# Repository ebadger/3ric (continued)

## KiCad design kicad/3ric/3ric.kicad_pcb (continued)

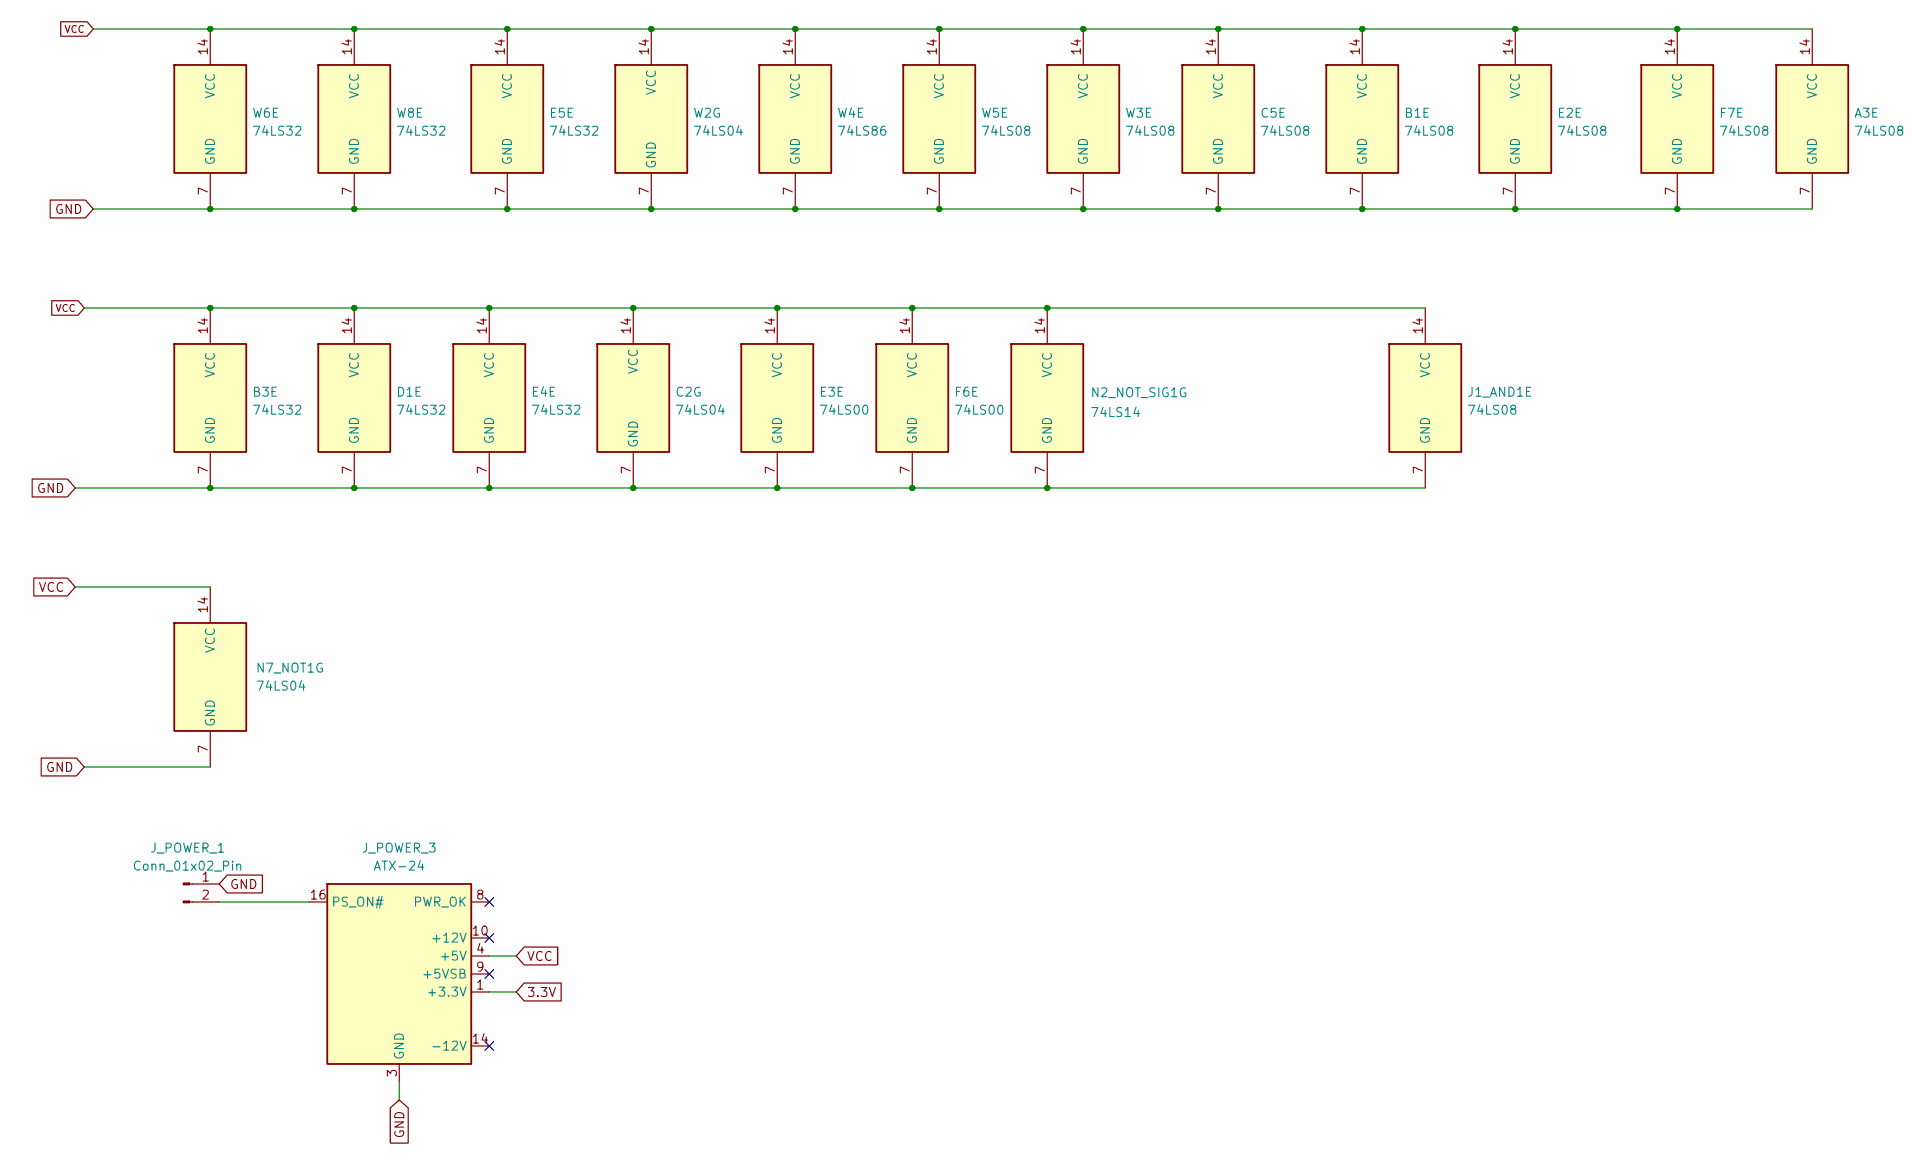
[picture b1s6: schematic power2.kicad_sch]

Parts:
A3: 74LS08; DIP-14_W7.62mm_Socket
B1: 74LS08; DIP-14_W7.62mm_Socket
B3: 74LS32; DIP-14_W7.62mm_Socket
C2: 74LS04; DIP-14_W7.62mm_Socket
C5: 74LS08; DIP-14_W7.62mm_Socket
D1: 74LS32; DIP-14_W7.62mm_Socket
E2: 74LS08; DIP-14_W7.62mm_Socket
E3: 74LS00; DIP-14_W7.62mm_Socket
E4, E5: 74LS32; DIP-14_W7.62mm_Socket
F6: 74LS00; DIP-14_W7.62mm_Socket
F7: 74LS08; DIP-14_W7.62mm_Socket
J1_AND1: 74LS08; DIP-14_W7.62mm_Socket
J_POWER_1: Conn_01x02_Pin; PinHeader_2x01_P2.54mm_Vertical
J_POWER_3: ATX-24; 1-1775099-3
N2_NOT_SIG1: 74LS14; DIP-14_W7.62mm_Socket
N7_NOT1: 74LS04; DIP-14_W7.62mm_Socket
W2: 74LS04; DIP-14_W7.62mm_Socket
W3, W5: 74LS08; DIP-14_W7.62mm_Socket
W4: 74LS86; DIP-14_W7.62mm_Socket
W6, W8: 74LS32; DIP-14_W7.62mm_Socket

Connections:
3.3V: J_POWER_3.1 (+3.3V), J_POWER_3.2 (+3.3V), J_POWER_3.12 (+3.3V), J_POWER_3.13 (+3.3V); also elsewhere on the board
GND: A3.7 (GND), B1.7 (GND), B3.7 (GND), C2.7 (GND), C5.7 (GND), D1.7 (GND), E2.7 (GND), E3.7 (GND), E4.7 (GND), E5.7 (GND), F6.7 (GND), F7.7 (GND), J1_AND1.7 (GND), J_POWER_1.1, J_POWER_3.3 (GND), J_POWER_3.5 (GND), J_POWER_3.7 (GND), J_POWER_3.15 (GND), J_POWER_3.17 (GND), J_POWER_3.18 (GND), J_POWER_3.19 (GND), J_POWER_3.24 (GND), N2_NOT_SIG1.7 (GND), N7_NOT1.7 (GND), W2.7 (GND), W3.7 (GND), W4.7 (GND), W5.7 (GND), W6.7 (GND), W8.7 (GND); also elsewhere on the board
unnamed: J_POWER_1.2, J_POWER_3.16 (PS_ON#)
VCC: A3.14 (VCC), B1.14 (VCC), B3.14 (VCC), C2.14 (VCC), C5.14 (VCC), D1.14 (VCC), E2.14 (VCC), E3.14 (VCC), E4.14 (VCC), E5.14 (VCC), F6.14 (VCC), F7.14 (VCC), J1_AND1.14 (VCC), J_POWER_3.4 (+5V), J_POWER_3.6 (+5V), J_POWER_3.21 (+5V), J_POWER_3.22 (+5V), J_POWER_3.23 (+5V), N2_NOT_SIG1.14 (VCC), N7_NOT1.14 (VCC), W2.14 (VCC), W3.14 (VCC), W4.14 (VCC), W5.14 (VCC), W6.14 (VCC), W8.14 (VCC); also elsewhere on the board

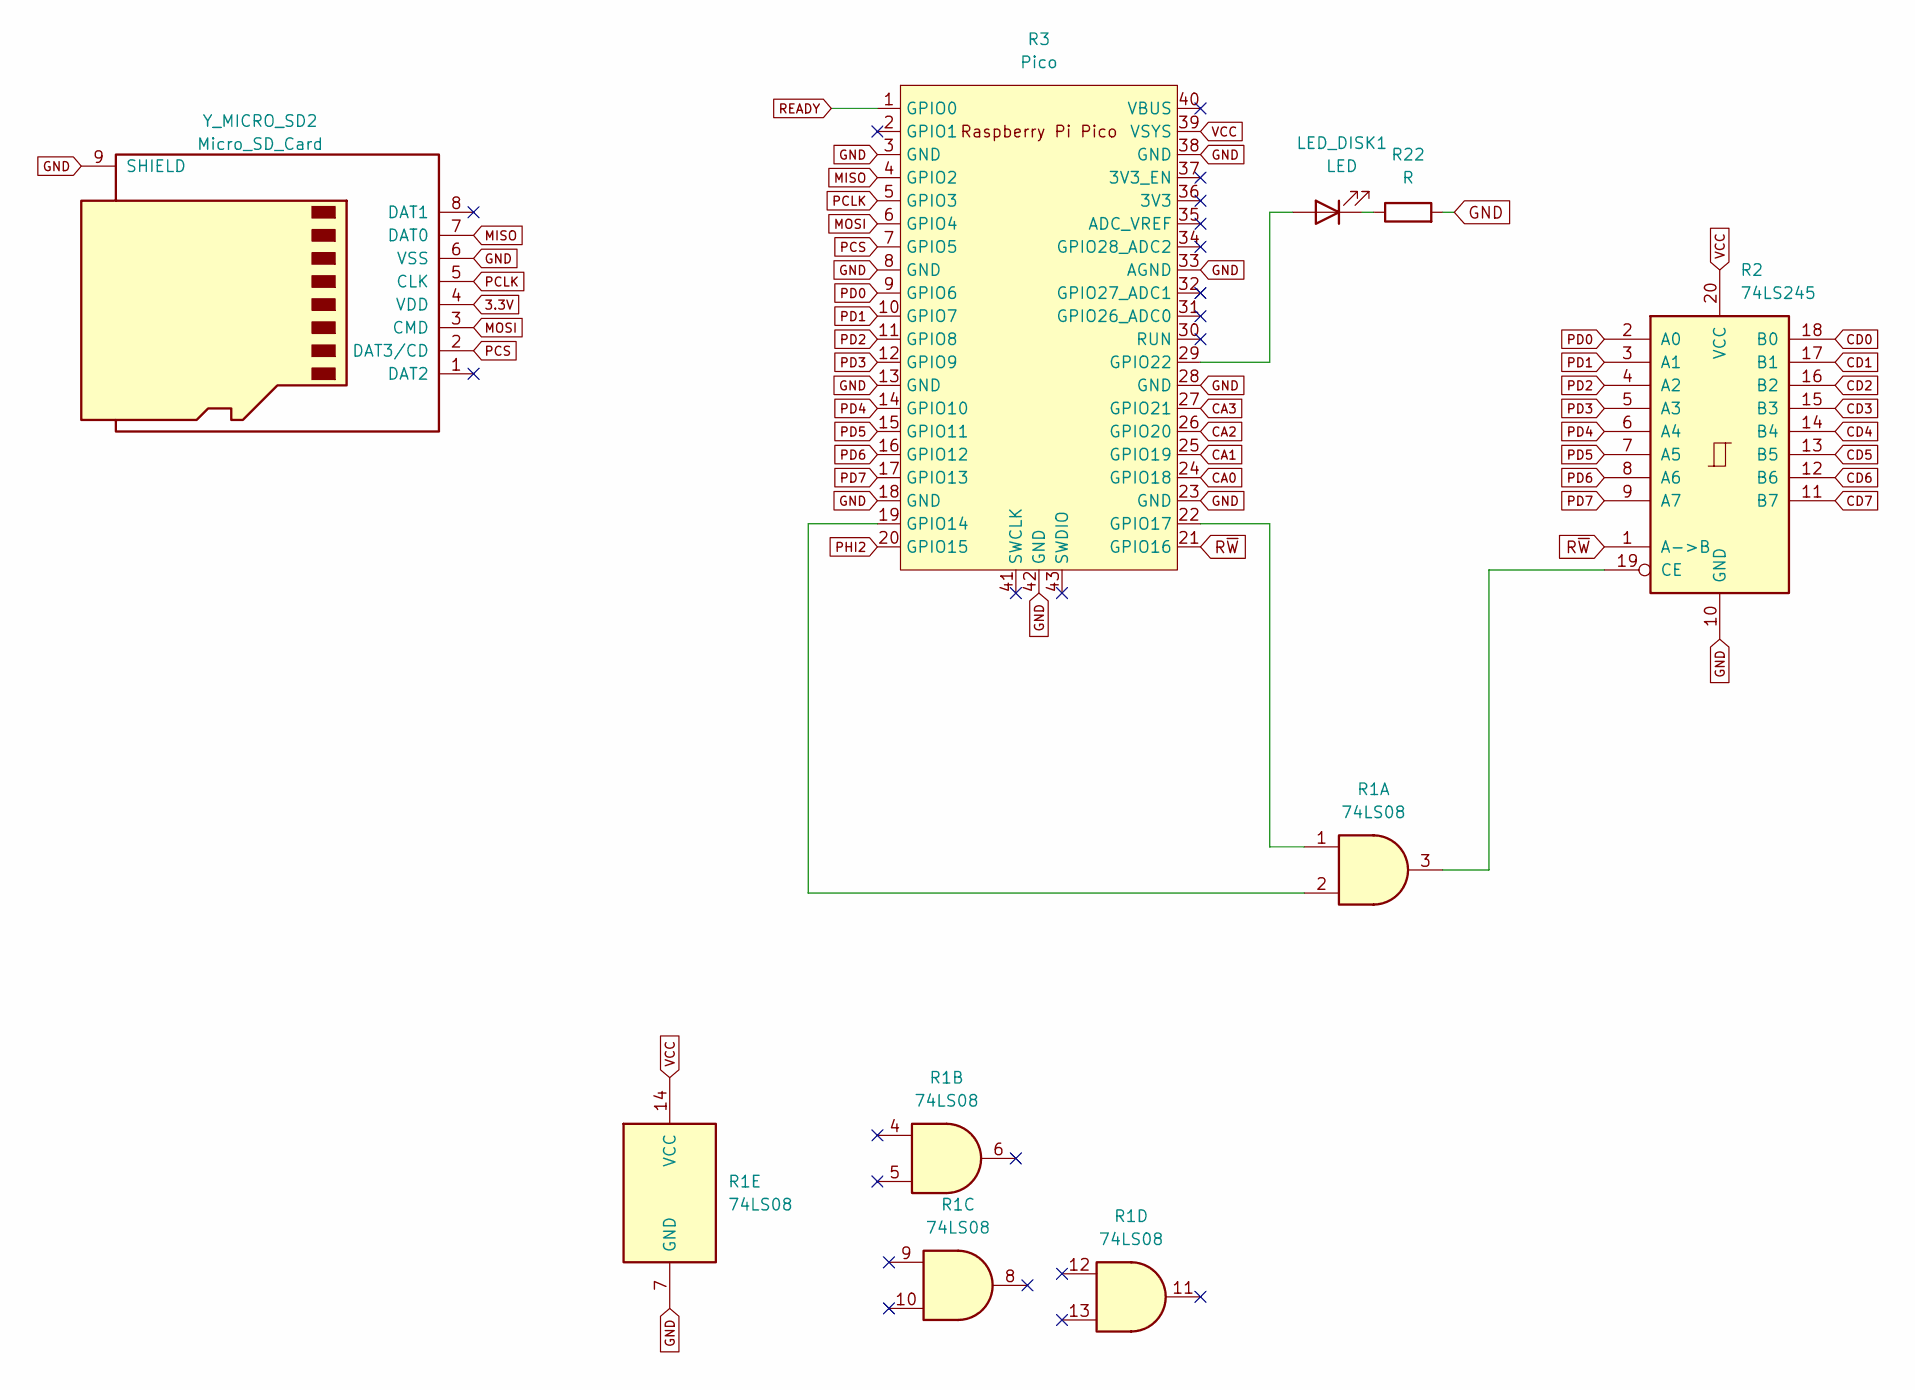
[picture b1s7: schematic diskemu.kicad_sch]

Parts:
LED_DISK1: LED; LED_D5.0mm
R1: 74LS08; DIP-14_W7.62mm_Socket
R2: 74LS245; DIP-20_W7.62mm_Socket
R3: Pico; RPi_Pico_SMD_TH
R22: R; R_0603_1608Metric_Pad0.98x0.95mm_HandSolder
Y_MICRO_SD2: Micro_SD_Card; microSD_Amazon2

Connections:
3.3V: Y_MICRO_SD2.4 (VDD); also elsewhere on the board
CA0: R3.24 (GPIO18); also elsewhere on the board
CA1: R3.25 (GPIO19); also elsewhere on the board
CA2: R3.26 (GPIO20); also elsewhere on the board
CA3: R3.27 (GPIO21); also elsewhere on the board
CD0: R2.18 (B0); also elsewhere on the board
CD1: R2.17 (B1); also elsewhere on the board
CD2: R2.16 (B2); also elsewhere on the board
CD3: R2.15 (B3); also elsewhere on the board
CD4: R2.14 (B4); also elsewhere on the board
CD5: R2.13 (B5); also elsewhere on the board
CD6: R2.12 (B6); also elsewhere on the board
CD7: R2.11 (B7); also elsewhere on the board
GND: R1.7 (GND), R2.10 (GND), R3.3 (GND), R3.8 (GND), R3.13 (GND), R3.18 (GND), R3.23 (GND), R3.28 (GND), R3.33 (AGND), R3.38 (GND), R3.42 (GND), R22.2, Y_MICRO_SD2.6 (VSS), Y_MICRO_SD2.9 (SHIELD); also elsewhere on the board
MISO: R3.4 (GPIO2), Y_MICRO_SD2.7 (DAT0)
MOSI: R3.6 (GPIO4), Y_MICRO_SD2.3 (CMD)
unnamed: LED_DISK1.2 (A), R3.29 (GPIO22)
unnamed: LED_DISK1.1 (K), R22.1
unnamed: R1.3, R2.19 (CE)
unnamed: R1.2, R3.19 (GPIO14)
unnamed: R1.1, R3.22 (GPIO17)
PCLK: R3.5 (GPIO3), Y_MICRO_SD2.5 (CLK)
PCS: R3.7 (GPIO5), Y_MICRO_SD2.2 (DAT3/CD)
PD0: R2.2 (A0), R3.9 (GPIO6)
PD1: R2.3 (A1), R3.10 (GPIO7)
PD2: R2.4 (A2), R3.11 (GPIO8)
PD3: R2.5 (A3), R3.12 (GPIO9)
PD4: R2.6 (A4), R3.14 (GPIO10)
PD5: R2.7 (A5), R3.15 (GPIO11)
PD6: R2.8 (A6), R3.16 (GPIO12)
PD7: R2.9 (A7), R3.17 (GPIO13)
PHI2: R3.20 (GPIO15); also elsewhere on the board
READY: R3.1 (GPIO0); also elsewhere on the board
R~W: R2.1 (A->B), R3.21 (GPIO16); also elsewhere on the board
VCC: R1.14 (VCC), R2.20 (VCC), R3.39 (VSYS); also elsewhere on the board

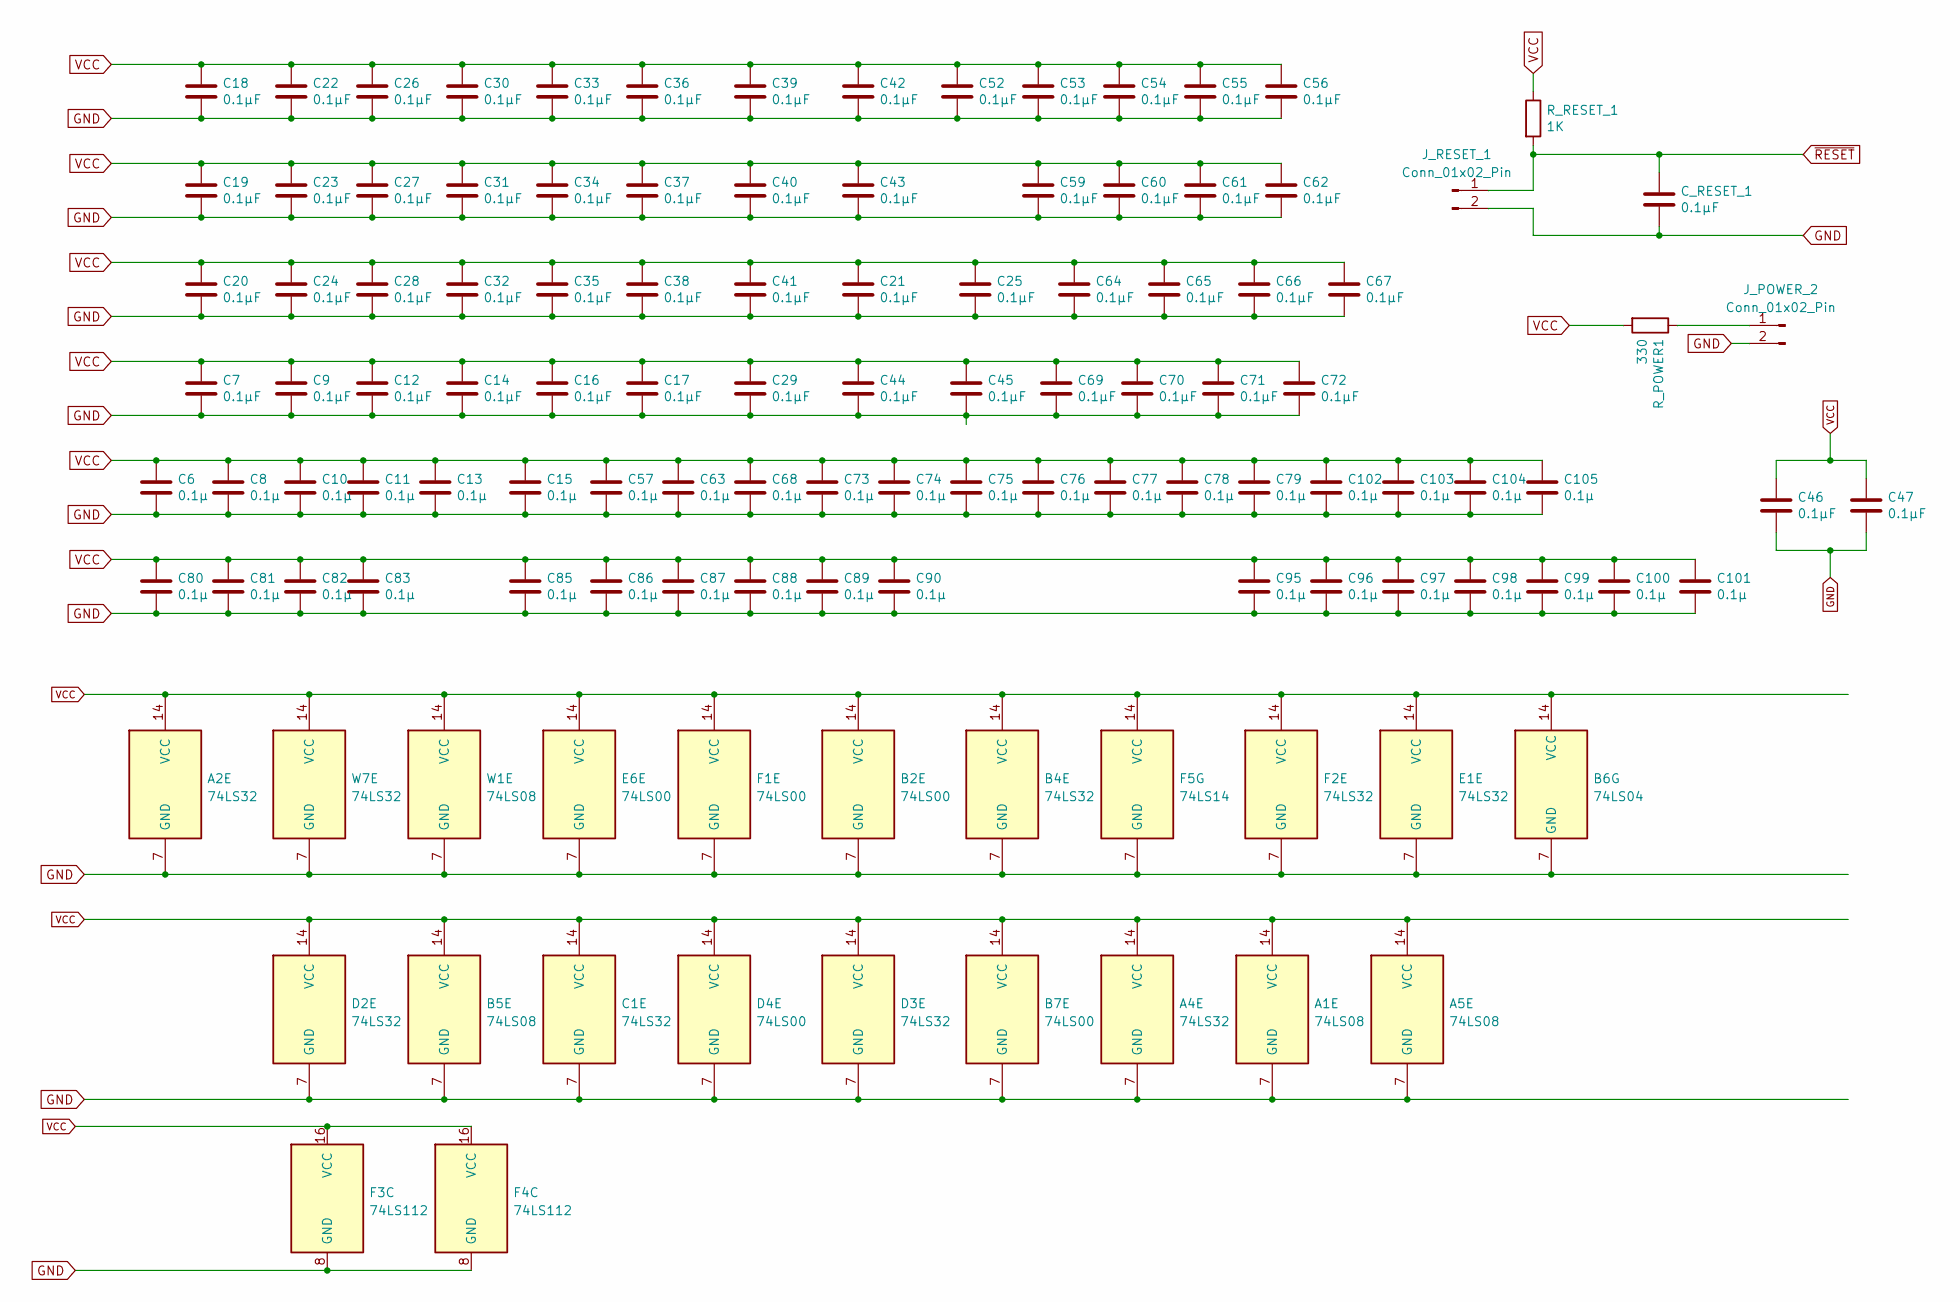
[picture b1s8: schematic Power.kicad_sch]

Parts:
A1, A5: 74LS08; DIP-14_W7.62mm_Socket
A2, A4: 74LS32; DIP-14_W7.62mm_Socket
B2, B7: 74LS00; DIP-14_W7.62mm_Socket
B4: 74LS32; DIP-14_W7.62mm_Socket
B5: 74LS08; DIP-14_W7.62mm_Socket
B6: 74LS04; DIP-14_W7.62mm_Socket
C1: 74LS32; DIP-14_W7.62mm_Socket
C6, C8, C10, C11, C13, C15, C57, C63, C68, C73, C74, C75, C76, C77, C78, C79, C80, C81, C82, C83, C85, C86, C87, C88, C89, C90, C95, C96, C97, C98, C99, C100, C101, C102, C103, C104, C105: 0.1µ; C_1206_3216Metric_Pad1.33x1.80mm_HandSolder
C7, C9, C12, C14, C16, C17, C18, C19, C20, C21, C22, C23, C24, C25, C26, C27, C28, C29, C30, C31, C32, C33, C34, C35, C36, C37, C38, C39, C40, C41, C42, C43, C44, C45, C46, C47, C52, C53, C54, C55, C56, C59, C60, C61, C62, C64, C65, C66, C67, C69, C70, C71, C72: 0.1µF; C_1206_3216Metric_Pad1.33x1.80mm_HandSolder
C_RESET_1: 0.1µF; C_1206_3216Metric_Pad1.33x1.80mm_HandSolder
D2, D3: 74LS32; DIP-14_W7.62mm_Socket
D4: 74LS00; DIP-14_W7.62mm_Socket
E1: 74LS32; DIP-14_W7.62mm_Socket
E6: 74LS00; DIP-14_W7.62mm_Socket
F1: 74LS00; DIP-14_W7.62mm_Socket
F2: 74LS32; DIP-14_W7.62mm_Socket
F3, F4: 74LS112; DIP-16_W7.62mm_Socket
F5: 74LS14; DIP-14_W7.62mm_Socket
J_POWER_2: Conn_01x02_Pin; PinHeader_2x01_P2.54mm_Vertical
J_RESET_1: Conn_01x02_Pin; PinHeader_2x01_P2.54mm_Vertical
R_POWER1: 330; R_0603_1608Metric_Pad0.98x0.95mm_HandSolder
R_RESET_1: 1K; R_0805_2012Metric_Pad1.20x1.40mm_HandSolder
W1: 74LS08; DIP-14_W7.62mm_Socket
W7: 74LS32; DIP-14_W7.62mm_Socket

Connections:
GND: A1.7 (GND), A2.7 (GND), A4.7 (GND), A5.7 (GND), B2.7 (GND), B4.7 (GND), B5.7 (GND), B6.7 (GND), B7.7 (GND), C1.7 (GND), C6.2, C7.2, C8.2, C9.2, C10.2, C11.2, C12.2, C13.2, C14.2, C15.2, C16.2, C17.2, C18.2, C19.2, C20.2, C21.2, C22.2, C23.2, C24.2, C25.2, C26.2, C27.2, C28.2, C29.2, C30.2, C31.2, C32.2, C33.2, C34.2, C35.2, C36.2, C37.2, C38.2, C39.2, C40.2, C41.2, C42.2, C43.2, C44.2, C45.2, C46.2, C47.2, C52.2, C53.2, C54.2, C55.2, C56.2, C57.2, C59.2, C60.2, C61.2, C62.2, C63.2, C64.2, C65.2, C66.2, C67.2, C68.2, C69.2, C70.2, C71.2, C72.2, C73.2, C74.2, C75.2, C76.2, C77.2, C78.2, C79.2, C80.2, C81.2, C82.2, C83.2, C85.2, C86.2, C87.2, C88.2, C89.2, C90.2, C95.2, C96.2, C97.2, C98.2, C99.2, C100.2, C101.2, C102.2, C103.2, C104.2, C105.2, C_RESET_1.2, D2.7 (GND), D3.7 (GND), D4.7 (GND), E1.7 (GND), E6.7 (GND), F1.7 (GND), F2.7 (GND), F3.8 (GND), F4.8 (GND), F5.7 (GND), J_POWER_2.2, J_RESET_1.2, W1.7 (GND), W7.7 (GND); also elsewhere on the board
unnamed: J_POWER_2.1, R_POWER1.1
VCC: A1.14 (VCC), A2.14 (VCC), A4.14 (VCC), A5.14 (VCC), B2.14 (VCC), B4.14 (VCC), B5.14 (VCC), B6.14 (VCC), B7.14 (VCC), C1.14 (VCC), C6.1, C7.1, C8.1, C9.1, C10.1, C11.1, C12.1, C13.1, C14.1, C15.1, C16.1, C17.1, C18.1, C19.1, C20.1, C21.1, C22.1, C23.1, C24.1, C25.1, C26.1, C27.1, C28.1, C29.1, C30.1, C31.1, C32.1, C33.1, C34.1, C35.1, C36.1, C37.1, C38.1, C39.1, C40.1, C41.1, C42.1, C43.1, C44.1, C45.1, C46.1, C47.1, C52.1, C53.1, C54.1, C55.1, C56.1, C57.1, C59.1, C60.1, C61.1, C62.1, C63.1, C64.1, C65.1, C66.1, C67.1, C68.1, C69.1, C70.1, C71.1, C72.1, C73.1, C74.1, C75.1, C76.1, C77.1, C78.1, C79.1, C80.1, C81.1, C82.1, C83.1, C85.1, C86.1, C87.1, C88.1, C89.1, C90.1, C95.1, C96.1, C97.1, C98.1, C99.1, C100.1, C101.1, C102.1, C103.1, C104.1, C105.1, D2.14 (VCC), D3.14 (VCC), D4.14 (VCC), E1.14 (VCC), E6.14 (VCC), F1.14 (VCC), F2.14 (VCC), F3.16 (VCC), F4.16 (VCC), F5.14 (VCC), R_POWER1.2, R_RESET_1.1, W1.14 (VCC), W7.14 (VCC); also elsewhere on the board
~RESET: C_RESET_1.1, J_RESET_1.1, R_RESET_1.2; also elsewhere on the board

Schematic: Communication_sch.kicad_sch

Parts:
H1_LEVEL_SHIFT1: ETSSOP-20-1EP_4.4x6.5mm_P0.65mm_EP3x4.2mm
H2_ACIA_CLK1: 1.8432MHz; Oscillator_DIP-14
I1_VIA1: 65C22S; DIP-40_W15.24mm_Socket
J4_ACIA1: 6502-library_65C51N; DIP-28_W15.24mm_Socket
J5, J6: Conn_02x08_Odd_Even; PinHeader_2x08_P2.54mm_Vertical
RKB1, RKB2: R; R_0805_2012Metric_Pad1.20x1.40mm_HandSolder
RM1, RM2: R; R_0805_2012Metric_Pad1.20x1.40mm_HandSolder
Y_MICRO_SD1: Micro_SD_Card; microSD_Amazon2
Y_PS2_KB1: PS/2 keyboard; MINI-DIN-6-FULL-SHIELD
Y_PS2_MOUSE1: PS/2 Mouse; MINI-DIN-6-FULL-SHIELD
Y_SERIAL_PINS1: PinHeader_2x03_P2.54mm_Vertical
Y_SNES_1, Y_SNES_2: SNES_Controller_Socket

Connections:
3.3V: H1_LEVEL_SHIFT1.2 (VCCA), Y_MICRO_SD1.4 (VDD); also elsewhere on the board
C010: I1_VIA1.18 (CB1); also elsewhere on the board
C070: I1_VIA1.19 (CB2); also elsewhere on the board
CA0: I1_VIA1.38 (RS0), J4_ACIA1.13 (RS0), J5.1; also elsewhere on the board
CA1: I1_VIA1.37 (RS1), J4_ACIA1.14 (RS1), J5.3; also elsewhere on the board
CA2: I1_VIA1.36 (RS2), J5.5; also elsewhere on the board
CA3: I1_VIA1.35 (RS3), J5.7; also elsewhere on the board
CA4: J5.9; also elsewhere on the board
CA5: J5.11; also elsewhere on the board
CA6: J5.13; also elsewhere on the board
CA7: J5.15; also elsewhere on the board
CA8: J5.10; also elsewhere on the board
CA9: J5.12; also elsewhere on the board
CA10: J5.14; also elsewhere on the board
CA11: J5.16; also elsewhere on the board
CA12: J5.8; also elsewhere on the board
CA13: J5.6; also elsewhere on the board
CA14: J5.4; also elsewhere on the board
CA15: J5.2; also elsewhere on the board
CD0: I1_VIA1.33 (D0), J4_ACIA1.18 (D0), J6.6; also elsewhere on the board
CD1: I1_VIA1.32 (D1), J4_ACIA1.19 (D1), J6.4; also elsewhere on the board
CD2: I1_VIA1.31 (D2), J4_ACIA1.20 (D2), J6.2; also elsewhere on the board
CD3: I1_VIA1.30 (D3), J4_ACIA1.21 (D3), J6.8; also elsewhere on the board
CD4: I1_VIA1.29 (D4), J4_ACIA1.22 (D4), J6.10; also elsewhere on the board
CD5: I1_VIA1.28 (D5), J4_ACIA1.23 (D5), J6.12; also elsewhere on the board
CD6: I1_VIA1.27 (D6), J4_ACIA1.24 (D6), J6.14; also elsewhere on the board
CD7: I1_VIA1.26 (D7), J4_ACIA1.25 (D7), J6.16; also elsewhere on the board
CLK_KB: I1_VIA1.8 (PA6), I1_VIA1.39 (CA2), RKB1.2, Y_PS2_KB1.5
CLK_MOUSE: I1_VIA1.11 (PB1), I1_VIA1.40 (CA1), RM1.2, Y_PS2_MOUSE1.5
DATA_KB: I1_VIA1.9 (PA7), RKB2.1, Y_PS2_KB1.1
DATA_MOUSE: I1_VIA1.10 (PB0), RM2.1, Y_PS2_MOUSE1.1
GC_CLOCK: I1_VIA1.17 (PB7), Y_SNES_1.2 (Clock), Y_SNES_2.2 (Clock)
GC_DATA1: I1_VIA1.15 (PB5), Y_SNES_1.4 (Data)
GC_DATA2: I1_VIA1.14 (PB4), Y_SNES_2.4 (Data)
GC_LATCH: I1_VIA1.16 (PB6), Y_SNES_1.3 (Latch), Y_SNES_2.3 (Latch)
GND: H1_LEVEL_SHIFT1.11 (GND), H2_ACIA_CLK1.7 (GND), I1_VIA1.1 (VSS), J4_ACIA1.1 (VSS), J6.5, Y_MICRO_SD1.6 (VSS), Y_MICRO_SD1.9 (SHIELD), Y_PS2_KB1.3, Y_PS2_MOUSE1.3, Y_SERIAL_PINS1.2, Y_SNES_1.7 (GND), Y_SNES_2.7 (GND); also elsewhere on the board
unnamed: H1_LEVEL_SHIFT1.1 (A1), Y_MICRO_SD1.7 (DAT0)
unnamed: H1_LEVEL_SHIFT1.3 (A2), Y_MICRO_SD1.3 (CMD)
unnamed: H1_LEVEL_SHIFT1.4 (A3), Y_MICRO_SD1.5 (CLK)
unnamed: H1_LEVEL_SHIFT1.5 (A4), Y_MICRO_SD1.2 (DAT3/CD)
unnamed: H1_LEVEL_SHIFT1.20 (B1), I1_VIA1.3 (PA1)
unnamed: H1_LEVEL_SHIFT1.18 (B2), I1_VIA1.4 (PA2)
unnamed: H1_LEVEL_SHIFT1.17 (B3), I1_VIA1.5 (PA3)
unnamed: H1_LEVEL_SHIFT1.16 (B4), I1_VIA1.6 (PA4)
unnamed: H2_ACIA_CLK1.8 (OUT), J4_ACIA1.6 (XTLI)
PHI2: I1_VIA1.25 (PHI2), J4_ACIA1.27 (PHI2), J6.11; also elsewhere on the board
RXD: J4_ACIA1.12 (RxD), Y_SERIAL_PINS1.5
R~W: I1_VIA1.22 (R~W), J4_ACIA1.28 (R~W), J6.13; also elsewhere on the board
TXD: J4_ACIA1.10 (TxD), Y_SERIAL_PINS1.6
V1_A0: I1_VIA1.2 (PA0)
V1_B2: I1_VIA1.12 (PB2)
V1_B3: I1_VIA1.13 (PB3)
VCC: H1_LEVEL_SHIFT1.10 (OE), H1_LEVEL_SHIFT1.19 (VCCB), H2_ACIA_CLK1.14 (Vcc), I1_VIA1.20 (VDD), I1_VIA1.24 (CS1), J4_ACIA1.2 (CS0), J4_ACIA1.15 (VDD), J6.15, RKB1.1, RKB2.2, RM1.1, RM2.2, Y_PS2_KB1.4, Y_PS2_MOUSE1.4, Y_SERIAL_PINS1.1, Y_SNES_1.1 (VCC), Y_SNES_2.1 (VCC); also elsewhere on the board
~CS_ACIA: J4_ACIA1.3 (~CS1); also elsewhere on the board
~CS_IO5: J6.3; also elsewhere on the board
~CS_IO7: J6.1; also elsewhere on the board
~CS_VIA1: I1_VIA1.23 (~CS2); also elsewhere on the board
~CTS: J4_ACIA1.9 (~CTS), Y_SERIAL_PINS1.4
~IRQEXT: J6.9; also elsewhere on the board
~IRQ_ACIA: J4_ACIA1.26 (~IRQ); also elsewhere on the board
~IRQ_VIA1: I1_VIA1.21 (~IRQ); also elsewhere on the board
~NMIEXT: J6.7; also elsewhere on the board
~RESET: I1_VIA1.34 (~RES), J4_ACIA1.4 (~RES); also elsewhere on the board
~RTS: J4_ACIA1.8 (~RTS), Y_SERIAL_PINS1.3

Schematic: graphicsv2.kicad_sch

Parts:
D20, D21, D22, D23, D24: D; D_SMA-SMB_Universal_Handsoldering
R_BLUE_220: 220; R_0603_1608Metric_Pad0.98x0.95mm_HandSolder
R_BLUE_500: 500; R_0805_2012Metric_Pad1.20x1.40mm_HandSolder
R_DOWN1: 100; R_0402_1005Metric_Pad0.72x0.64mm_HandSolder
R_GREEN_220: 220; R_0603_1608Metric_Pad0.98x0.95mm_HandSolder
R_GREEN_500: 500; R_0805_2012Metric_Pad1.20x1.40mm_HandSolder
R_RED_220: 220; R_0603_1608Metric_Pad0.98x0.95mm_HandSolder
R_RED_500: 500; R_0805_2012Metric_Pad1.20x1.40mm_HandSolder
U1_VID_SHIFT1, U2_PIXEL_LATCH1, U3_LOWRES_OUT1: DIP-20_W7.62mm_Socket
U4_ODD_BIT1: DIP-16_W7.62mm_Socket
V1_PALETTE_LATCH1, V2_PHI16_LATCH1: DIP-20_W7.62mm_Socket
W1, W3, W5: 74LS08; DIP-14_W7.62mm_Socket
W2: 74LS04; DIP-14_W7.62mm_Socket
W4: 74LS86; DIP-14_W7.62mm_Socket
W6, W7, W8: 74LS32; DIP-14_W7.62mm_Socket
Y_VGA1: DB15_Female_HighDensity; DSUB-15-HD_Female_Horizontal_P2.29x1.98mm_EdgePinOffset8.35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

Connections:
!DISPLAY2: V2_PHI16_LATCH1.1 (OE), W7.13; also elsewhere on the board
!GFXSHIFT: U1_VID_SHIFT1.9 (Mr); also elsewhere on the board
B1: D22.1 (K), R_BLUE_220.1, U3_LOWRES_OUT1.14 (Q5); also elsewhere on the board
B2: D23.1 (K), R_BLUE_500.1, U3_LOWRES_OUT1.15 (Q4); also elsewhere on the board
CYAN: W5.11, W6.10, W6.12, W7.1
CurrPix: U2_PIXEL_LATCH1.4 (D2), U2_PIXEL_LATCH1.18 (Q1), W1.2
DISP3OUT: U2_PIXEL_LATCH1.15 (Q4), W1.1, W1.4
DISPLAY3: U2_PIXEL_LATCH1.6 (D4), U4_ODD_BIT1.1 (~MR); also elsewhere on the board
G1: D20.1 (K), R_GREEN_220.1, U3_LOWRES_OUT1.16 (Q3)
G2: D21.1 (K), R_GREEN_500.1, U3_LOWRES_OUT1.17 (Q2)
GFXLOAD: U1_VID_SHIFT1.19 (S1), U3_LOWRES_OUT1.11 (Cp); also elsewhere on the board
GND: R_DOWN1.2, U1_VID_SHIFT1.10 (GND), U1_VID_SHIFT1.11 (Ds0), U1_VID_SHIFT1.18 (Ds7), U2_PIXEL_LATCH1.1 (OE), U2_PIXEL_LATCH1.7 (D5), U2_PIXEL_LATCH1.8 (D6), U2_PIXEL_LATCH1.9 (D7), U2_PIXEL_LATCH1.10 (GND), U3_LOWRES_OUT1.10 (GND), U4_ODD_BIT1.3 (D0), U4_ODD_BIT1.4 (D1), U4_ODD_BIT1.5 (D2), U4_ODD_BIT1.6 (D3), U4_ODD_BIT1.8 (GND), V1_PALETTE_LATCH1.1 (OE), V1_PALETTE_LATCH1.10 (GND), V2_PHI16_LATCH1.10 (GND), Y_VGA1.5, Y_VGA1.6, Y_VGA1.7, Y_VGA1.8, Y_VGA1.10; also elsewhere on the board
GREEN: W5.6, W6.5, W8.10
HGR_B1: D22.2 (A), W8.11
HGR_B2: D23.2 (A), W8.3
HGR_G1: D20.2 (A), W8.6
HGR_G2: D21.2 (A), W8.8
HGR_R1: D24.2 (A), W7.8
HSYNC: Y_VGA1.13; also elsewhere on the board
LOWOUT: U3_LOWRES_OUT1.1 (OE), W7.11
LOWSHIFT: W7.12; also elsewhere on the board
unnamed: R_BLUE_220.2, R_BLUE_500.2, Y_VGA1.3
unnamed: R_GREEN_220.2, R_GREEN_500.2, Y_VGA1.2
unnamed: R_RED_220.2, R_RED_500.2, Y_VGA1.1
unnamed: U1_VID_SHIFT1.17 (Q7), U2_PIXEL_LATCH1.3 (D1)
unnamed: W1.3, W2.1, W3.1, W3.4
unnamed: W1.6, W2.3, W3.5, W3.9
unnamed: W1.8, W4.5, W4.9
unnamed: W1.10, W4.3
unnamed: W2.2, W3.10
unnamed: W2.4, W3.2
unnamed: W2.6, W5.5, W5.9
unnamed: W3.3, W4.1, W4.4
unnamed: W3.8, W4.2, W4.10
unnamed: W4.6, W5.1, W5.4
unnamed: W4.8, W5.10, W5.12
unnamed: W6.3, W6.9, W7.10
unnamed: W6.6, W7.2
unnamed: W6.8, W8.12
unnamed: W6.11, W8.1
unnamed: W7.3, W8.4
unnamed: W7.6, W7.9, W8.2, W8.5, W8.9, W8.13
ORANGE: W5.3, W6.1, W6.4
OddBit1: U2_PIXEL_LATCH1.5 (D3), U4_ODD_BIT1.14 (Q0)
OddBit2: U2_PIXEL_LATCH1.16 (Q3), W1.9
PAL_IN: U2_PIXEL_LATCH1.2 (D0), V1_PALETTE_LATCH1.12 (Q7)
PHI7: U1_VID_SHIFT1.12 (Cp), U2_PIXEL_LATCH1.11 (Cp), U4_ODD_BIT1.2 (CP); also elsewhere on the board
PHI16: V2_PHI16_LATCH1.11 (Cp); also elsewhere on the board
Palette: U2_PIXEL_LATCH1.19 (Q0), W2.5, W5.2, W5.13
PrevPix: U2_PIXEL_LATCH1.17 (Q2), W1.5
R1: D24.1 (K), R_RED_220.1, U3_LOWRES_OUT1.18 (Q1)
R2: R_RED_500.1, U3_LOWRES_OUT1.19 (Q0)
SHIFT_TXT: V2_PHI16_LATCH1.2 (D0); also elsewhere on the board
SHIFT_TXT2: R_DOWN1.1, V2_PHI16_LATCH1.18 (Q1), W7.5
ST1: V2_PHI16_LATCH1.3 (D1), V2_PHI16_LATCH1.19 (Q0)
TD0: U3_LOWRES_OUT1.2 (D0); also elsewhere on the board
TD1: U3_LOWRES_OUT1.3 (D1); also elsewhere on the board
TD2: U3_LOWRES_OUT1.4 (D2); also elsewhere on the board
TD3: U3_LOWRES_OUT1.5 (D3); also elsewhere on the board
TD4: U3_LOWRES_OUT1.6 (D4); also elsewhere on the board
TD5: U3_LOWRES_OUT1.7 (D5); also elsewhere on the board
TD6: U3_LOWRES_OUT1.8 (D6); also elsewhere on the board
TD7: U3_LOWRES_OUT1.9 (D7); also elsewhere on the board
VCC: U1_VID_SHIFT1.1 (S0), U1_VID_SHIFT1.2 (OE1), U1_VID_SHIFT1.3 (OE2), U1_VID_SHIFT1.20 (VCC), U2_PIXEL_LATCH1.20 (VCC), U3_LOWRES_OUT1.20 (VCC), U4_ODD_BIT1.7 (CEP), U4_ODD_BIT1.9 (~PE), U4_ODD_BIT1.10 (CET), U4_ODD_BIT1.16 (VCC), V1_PALETTE_LATCH1.20 (VCC), V2_PHI16_LATCH1.20 (VCC); also elsewhere on the board
VIDENABLE: V1_PALETTE_LATCH1.11 (Cp); also elsewhere on the board
VIOLET: W5.8, W6.2, W6.13
VL0: V1_PALETTE_LATCH1.9 (D7); also elsewhere on the board
VL1: U1_VID_SHIFT1.13 (IO1); also elsewhere on the board
VL2: U1_VID_SHIFT1.6 (IO2); also elsewhere on the board
VL3: U1_VID_SHIFT1.14 (IO3); also elsewhere on the board
VL4: U1_VID_SHIFT1.5 (IO4); also elsewhere on the board
VL5: U1_VID_SHIFT1.15 (IO5); also elsewhere on the board
VL6: U1_VID_SHIFT1.4 (IO6); also elsewhere on the board
VL7: U1_VID_SHIFT1.16 (IO7); also elsewhere on the board
VSYNC: Y_VGA1.14; also elsewhere on the board
WHITE: W3.6, W7.4

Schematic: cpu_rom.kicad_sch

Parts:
J1_AND1: 74LS08; DIP-14_W7.62mm_Socket
J3_DEV_DECODE1: 74LS154; DIP-24_W15.24mm_Socket
K1_CPU1: 6502-library_65C02S-2; DIP-40_W15.24mm_Socket
K2_ROM1: SST39SF040; DIP-32_W15.24mm_Socket
R4, R5, R6: 1K; R_0402_1005Metric_Pad0.72x0.64mm_HandSolder
R26, R27, R28, R29, R30, R31: 1K; R_0805_2012Metric_Pad1.20x1.40mm_HandSolder

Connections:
C6XX: J3_DEV_DECODE1.7 (S6); also elsewhere on the board
CA0: K1_CPU1.9 (A0), K2_ROM1.12 (A0); also elsewhere on the board
CA1: K1_CPU1.10 (A1), K2_ROM1.11 (A1); also elsewhere on the board
CA2: K1_CPU1.11 (A2), K2_ROM1.10 (A2); also elsewhere on the board
CA3: K1_CPU1.12 (A3), K2_ROM1.9 (A3); also elsewhere on the board
CA4: K1_CPU1.13 (A4), K2_ROM1.8 (A4); also elsewhere on the board
CA5: K1_CPU1.14 (A5), K2_ROM1.7 (A5); also elsewhere on the board
CA6: K1_CPU1.15 (A6), K2_ROM1.6 (A6); also elsewhere on the board
CA7: K1_CPU1.16 (A7), K2_ROM1.5 (A7); also elsewhere on the board
CA8: J3_DEV_DECODE1.23 (A0), K1_CPU1.17 (A8), K2_ROM1.27 (A8); also elsewhere on the board
CA9: J3_DEV_DECODE1.22 (A1), K1_CPU1.18 (A9), K2_ROM1.26 (A9); also elsewhere on the board
CA10: J3_DEV_DECODE1.21 (A2), K1_CPU1.19 (A10), K2_ROM1.23 (A10); also elsewhere on the board
CA11: J3_DEV_DECODE1.20 (A3), K1_CPU1.20 (A11), K2_ROM1.25 (A11); also elsewhere on the board
CA12: K1_CPU1.22 (A12), K2_ROM1.4 (A12); also elsewhere on the board
CA13: K1_CPU1.23 (A13), K2_ROM1.28 (A13); also elsewhere on the board
CA14: K1_CPU1.24 (A14), K2_ROM1.29 (A14); also elsewhere on the board
CA15: K1_CPU1.25 (A15), K2_ROM1.3 (A15); also elsewhere on the board
CD0: K1_CPU1.33 (D0), K2_ROM1.13 (D0); also elsewhere on the board
CD1: K1_CPU1.32 (D1), K2_ROM1.14 (D1); also elsewhere on the board
CD2: K1_CPU1.31 (D2), K2_ROM1.15 (D2); also elsewhere on the board
CD3: K1_CPU1.30 (D3), K2_ROM1.17 (D3); also elsewhere on the board
CD4: K1_CPU1.29 (D4), K2_ROM1.18 (D4); also elsewhere on the board
CD5: K1_CPU1.28 (D5), K2_ROM1.19 (D5); also elsewhere on the board
CD6: K1_CPU1.27 (D6), K2_ROM1.20 (D6); also elsewhere on the board
CD7: K1_CPU1.26 (D7), K2_ROM1.21 (D7); also elsewhere on the board
GND: J3_DEV_DECODE1.12 (GND), K1_CPU1.21 (GND), K2_ROM1.16 (GND); also elsewhere on the board
unnamed: J1_AND1.3, J1_AND1.4
unnamed: J1_AND1.8, J1_AND1.12
unnamed: K1_CPU1.36 (BE), R6.1
unnamed: K1_CPU1.38 (~SO), R5.1
PHI2: K1_CPU1.37 (PHI2); also elsewhere on the board
READY: K1_CPU1.2 (RDY), R4.1; also elsewhere on the board
ROM1: K2_ROM1.1 (A18); also elsewhere on the board
ROM2: K2_ROM1.30 (A17); also elsewhere on the board
ROM3: K2_ROM1.2 (A16); also elsewhere on the board
R~W: K1_CPU1.34 (R/~W); also elsewhere on the board
VCC: J3_DEV_DECODE1.24 (VCC), K1_CPU1.8 (VCC), K2_ROM1.31 (PGM), K2_ROM1.32 (VCC), R4.2, R5.2, R6.2, R26.2, R27.2, R28.2, R29.2, R30.2, R31.2; also elsewhere on the board
~CS_ACIA: J3_DEV_DECODE1.2 (S1); also elsewhere on the board
~CS_DEVICE: J3_DEV_DECODE1.18 (E0), J3_DEV_DECODE1.19 (E1); also elsewhere on the board
~CS_IO5: J3_DEV_DECODE1.6 (S5); also elsewhere on the board
~CS_IO7: J3_DEV_DECODE1.8 (S7); also elsewhere on the board
~CS_MB: J3_DEV_DECODE1.5 (S4); also elsewhere on the board
~CS_ROM2: K2_ROM1.22 (CE); also elsewhere on the board
~CS_VIA1: J3_DEV_DECODE1.3 (S2); also elsewhere on the board
~IRQEXT: J1_AND1.13, R31.1; also elsewhere on the board
~IRQ_ACIA: J1_AND1.1, R26.1; also elsewhere on the board
~IRQ_MB1: J1_AND1.9, R30.1; also elsewhere on the board
~IRQ_MB2: J1_AND1.10, R29.1; also elsewhere on the board
~IRQ_VIA1: J1_AND1.2, R27.1; also elsewhere on the board
~IRQ: J1_AND1.11, K1_CPU1.4 (~IRQ)
~NMIEXT: J1_AND1.5, R28.1; also elsewhere on the board
~NMI: J1_AND1.6, K1_CPU1.6 (~NMI)
~OE: K2_ROM1.24 (OE); also elsewhere on the board
~RESET: K1_CPU1.40 (~RESET); also elsewhere on the board

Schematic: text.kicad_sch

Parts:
M1_VID_TXTSHIFT1: SN74LS166AN; DIP-16_W7.62mm_Socket
M4_ROM_FONTS1: SST39SF040; DIP-32_W15.24mm_Socket

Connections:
!LOWSHIFT: M4_ROM_FONTS1.1 (A18); also elsewhere on the board
!TEXTSHIFT: M1_VID_TXTSHIFT1.9 (*CLR); also elsewhere on the board
FS0: M4_ROM_FONTS1.4 (A12); also elsewhere on the board
FS1: M4_ROM_FONTS1.28 (A13); also elsewhere on the board
FS2: M4_ROM_FONTS1.29 (A14); also elsewhere on the board
FS3: M4_ROM_FONTS1.3 (A15); also elsewhere on the board
FS4: M4_ROM_FONTS1.2 (A16); also elsewhere on the board
FS5: M4_ROM_FONTS1.30 (A17); also elsewhere on the board
GND: M1_VID_TXTSHIFT1.8 (GND), M4_ROM_FONTS1.16 (GND), M4_ROM_FONTS1.22 (CE), M4_ROM_FONTS1.24 (OE); also elsewhere on the board
LOADSHIFT: M1_VID_TXTSHIFT1.15 (SH/*LD); also elsewhere on the board
PHI16: M1_VID_TXTSHIFT1.7 (CLK); also elsewhere on the board
SHIFT_TXT: M1_VID_TXTSHIFT1.13 (QH); also elsewhere on the board
TD0: M1_VID_TXTSHIFT1.2 (A), M4_ROM_FONTS1.13 (D0); also elsewhere on the board
TD1: M1_VID_TXTSHIFT1.3 (B), M4_ROM_FONTS1.14 (D1); also elsewhere on the board
TD2: M1_VID_TXTSHIFT1.4 (C), M4_ROM_FONTS1.15 (D2); also elsewhere on the board
TD3: M1_VID_TXTSHIFT1.5 (D), M4_ROM_FONTS1.17 (D3); also elsewhere on the board
TD4: M1_VID_TXTSHIFT1.10 (E), M4_ROM_FONTS1.18 (D4); also elsewhere on the board
TD5: M1_VID_TXTSHIFT1.11 (F), M4_ROM_FONTS1.19 (D5); also elsewhere on the board
TD6: M1_VID_TXTSHIFT1.12 (G), M4_ROM_FONTS1.20 (D6); also elsewhere on the board
TD7: M1_VID_TXTSHIFT1.14 (H), M4_ROM_FONTS1.21 (D7); also elsewhere on the board
TEXTSHIFT: M1_VID_TXTSHIFT1.6 (CLKINH); also elsewhere on the board
VCC: M1_VID_TXTSHIFT1.1 (SER), M1_VID_TXTSHIFT1.16 (VCC), M4_ROM_FONTS1.31 (PGM), M4_ROM_FONTS1.32 (VCC); also elsewhere on the board
VL0: M4_ROM_FONTS1.12 (A0); also elsewhere on the board
VL1: M4_ROM_FONTS1.11 (A1); also elsewhere on the board
VL2: M4_ROM_FONTS1.10 (A2); also elsewhere on the board
VL3: M4_ROM_FONTS1.9 (A3); also elsewhere on the board
VL4: M4_ROM_FONTS1.8 (A4); also elsewhere on the board
VL5: M4_ROM_FONTS1.7 (A5); also elsewhere on the board
VL6: M4_ROM_FONTS1.6 (A6); also elsewhere on the board
VL7: M4_ROM_FONTS1.5 (A7); also elsewhere on the board
VQ0: M4_ROM_FONTS1.27 (A8); also elsewhere on the board
VQ1: M4_ROM_FONTS1.26 (A9); also elsewhere on the board
VQ2: M4_ROM_FONTS1.23 (A10); also elsewhere on the board
VQ3: M4_ROM_FONTS1.25 (A11); also elsewhere on the board

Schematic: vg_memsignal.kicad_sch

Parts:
N1_SigLatch1: SN74LS279AN; DIP-16_W7.62mm_Socket
N2_NOT_SIG1: 74LS14; DIP-14_W7.62mm_Socket
O1_DECODE_SIGS1: 74LS154; DIP-24_W15.24mm_Socket

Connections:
!VIDENABLE: N1_SigLatch1.9 (3Q), N2_NOT_SIG1.1, N2_NOT_SIG1.11; also elsewhere on the board
GFXLOAD: N2_NOT_SIG1.6; also elsewhere on the board
GND: N1_SigLatch1.8 (GND), O1_DECODE_SIGS1.12 (GND), O1_DECODE_SIGS1.18 (E0), O1_DECODE_SIGS1.19 (E1); also elsewhere on the board
LOADSHIFT: N1_SigLatch1.4 (1Q); also elsewhere on the board
unnamed: N1_SigLatch1.13 (4Q), N2_NOT_SIG1.13
PHI2: O1_DECODE_SIGS1.20 (A3); also elsewhere on the board
PHI4: O1_DECODE_SIGS1.21 (A2); also elsewhere on the board
PHI8: O1_DECODE_SIGS1.22 (A1); also elsewhere on the board
PHI16: O1_DECODE_SIGS1.23 (A0); also elsewhere on the board
S0: N1_SigLatch1.11 (*3S1), N1_SigLatch1.12 (*3S2), N2_NOT_SIG1.5, O1_DECODE_SIGS1.1 (S0)
S1: N1_SigLatch1.15 (*4S), O1_DECODE_SIGS1.2 (S1)
S4: N1_SigLatch1.14 (*4R), O1_DECODE_SIGS1.5 (S4)
S5: N1_SigLatch1.10 (*3R), O1_DECODE_SIGS1.6 (S5)
S9: N1_SigLatch1.1 (*1R), O1_DECODE_SIGS1.10 (S9)
S10: N1_SigLatch1.2 (*1S1), N1_SigLatch1.3 (*1S2), O1_DECODE_SIGS1.11 (S10)
S11: N1_SigLatch1.5 (*2R), O1_DECODE_SIGS1.13 (S11)
S13: N1_SigLatch1.6 (*2S), O1_DECODE_SIGS1.15 (S13)
SS_WRITE_SIGNAL: N1_SigLatch1.7 (2Q); also elsewhere on the board
VCC: N1_SigLatch1.16 (VCC), O1_DECODE_SIGS1.24 (VCC); also elsewhere on the board
VIDBUS: N2_NOT_SIG1.12; also elsewhere on the board
VIDENABLE: N2_NOT_SIG1.10; also elsewhere on the board
VIDENABLE2: N2_NOT_SIG1.2; also elsewhere on the board

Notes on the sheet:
todo: update from breadboard
